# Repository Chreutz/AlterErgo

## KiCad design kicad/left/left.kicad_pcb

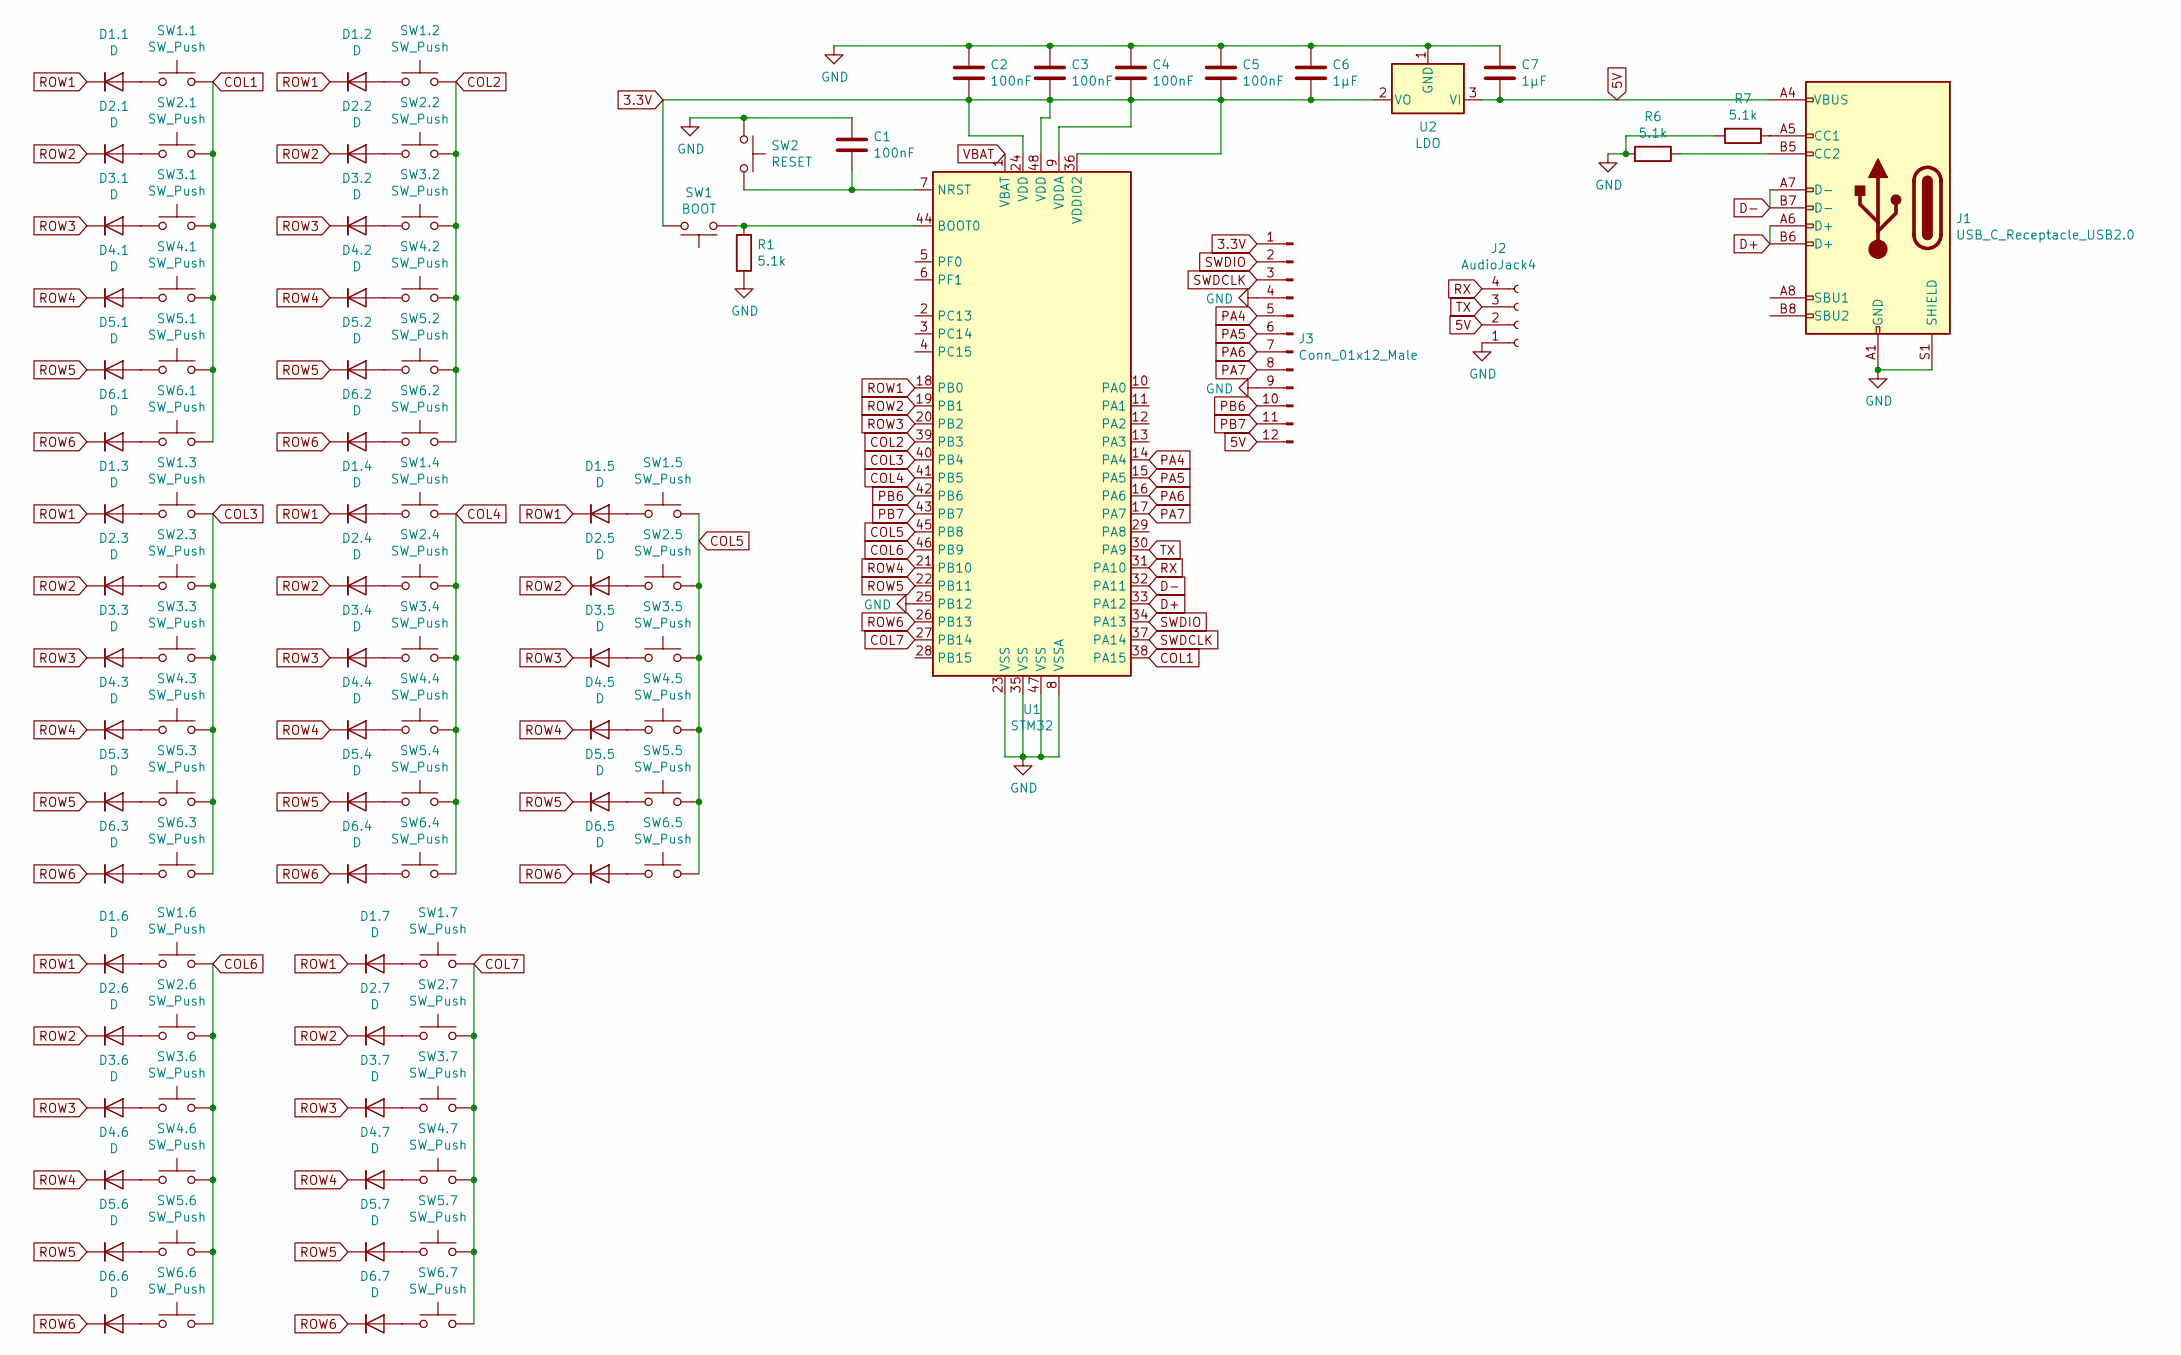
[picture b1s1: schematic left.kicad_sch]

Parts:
C1, C2, C3, C4, C5: 100nF; C_0805_2012Metric_Pad1.18x1.45mm_HandSolder
C6, C7: 1µF; C_0805_2012Metric_Pad1.18x1.45mm_HandSolder
D1.1, D1.2, D1.3, D1.4, D1.5, D1.6, D1.7, D2.1, D2.2, D2.3, D2.4, D2.5, D2.6, D2.7, D3.1, D3.2, D3.3, D3.4, D3.5, D3.6, D3.7, D4.1, D4.2, D4.3, D4.4, D4.5, D4.6, D4.7, D5.1, D5.2, D5.3, D5.4, D5.5, D5.6, D5.7, D6.1, D6.2, D6.3, D6.4, D6.5, D6.6, D6.7: D; D_SOD-323_HandSoldering
J1: USB_C_Receptacle_USB2.0; USB_C_Receptacle_HRO_TYPE-C-31-M-12
J2: AudioJack4; TRRS-PJ-320A-no-Fmask
J3: Conn_01x12_Male; Harwin_M20-89012xx_1x12_P2.54mm_Horizontal
R1, R6, R7: 5.1k; R_0805_2012Metric_Pad1.20x1.40mm_HandSolder
SW1: BOOT; SW_SPST_CK_RS282G05A3
SW1.1, SW1.2, SW1.3, SW1.4, SW1.5, SW1.6, SW1.7, SW2.1, SW2.2, SW2.3, SW2.4, SW2.5, SW2.6, SW2.7, SW3.1, SW3.2, SW3.3, SW3.4, SW3.5, SW3.6, SW3.7, SW4.1, SW4.2, SW4.3, SW4.4, SW4.5, SW4.6, SW4.7, SW5.1, SW5.2, SW5.3, SW5.4, SW5.5, SW5.6, SW5.7, SW6.1, SW6.2, SW6.3, SW6.4, SW6.5, SW6.6, SW6.7: SW_Push; CherryMX_Choc_1u
SW2: RESET; SW_SPST_CK_RS282G05A3
U1: STM32; LQFP-48_7x7mm_P0.5mm
U2: LDO; SOT-23

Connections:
3.3V: C2.2, C3.2, C4.2, C5.2, C6.2, J3.1, SW1.2, U1.9 (VDDA), U1.24 (VDD), U1.36 (VDDIO2), U1.48 (VDD), U2.2 (VO)
5V: C7.2, J1.A4 (VBUS), J1.A9 (VBUS), J1.B4 (VBUS), J1.B9 (VBUS), J2.2, J3.12, U2.3 (VI)
COL1: SW1.1.2, SW2.1.2, SW3.1.2, SW4.1.2, SW5.1.2, SW6.1.2, U1.38 (PA15)
COL2: SW1.2.2, SW2.2.2, SW3.2.2, SW4.2.2, SW5.2.2, SW6.2.2, U1.39 (PB3)
COL3: SW1.3.2, SW2.3.2, SW3.3.2, SW4.3.2, SW5.3.2, SW6.3.2, U1.40 (PB4)
COL4: SW1.4.2, SW2.4.2, SW3.4.2, SW4.4.2, SW5.4.2, SW6.4.2, U1.41 (PB5)
COL5: SW1.5.2, SW2.5.2, SW3.5.2, SW4.5.2, SW5.5.2, SW6.5.2, U1.45 (PB8)
COL6: SW1.6.2, SW2.6.2, SW3.6.2, SW4.6.2, SW5.6.2, SW6.6.2, U1.46 (PB9)
COL7: SW1.7.2, SW2.7.2, SW3.7.2, SW4.7.2, SW5.7.2, SW6.7.2, U1.27 (PB14)
D+: J1.A6 (D+), J1.B6 (D+), U1.33 (PA12)
D-: J1.A7 (D-), J1.B7 (D-), U1.32 (PA11)
GND: C1.1, C2.1, C3.1, C4.1, C5.1, C6.1, C7.1, J1.A1 (GND), J1.A12 (GND), J1.B1 (GND), J1.B12 (GND), J1.S1 (SHIELD), J2.1, J3.4, J3.9, R1.2, R6.2, R7.2, SW2.1, U1.8 (VSSA), U1.23 (VSS), U1.25 (PB12), U1.35 (VSS), U1.47 (VSS), U2.1 (GND)
unnamed: C1.2, SW2.2, U1.7 (NRST)
unnamed: D1.1.2 (A), SW1.1.1
unnamed: D1.2.2 (A), SW1.2.1
unnamed: D1.3.2 (A), SW1.3.1
unnamed: D1.4.2 (A), SW1.4.1
unnamed: D1.5.2 (A), SW1.5.1
unnamed: D1.6.2 (A), SW1.6.1
unnamed: D1.7.2 (A), SW1.7.1
unnamed: D2.1.2 (A), SW2.1.1
unnamed: D2.2.2 (A), SW2.2.1
unnamed: D2.3.2 (A), SW2.3.1
unnamed: D2.4.2 (A), SW2.4.1
unnamed: D2.5.2 (A), SW2.5.1
unnamed: D2.6.2 (A), SW2.6.1
unnamed: D2.7.2 (A), SW2.7.1
unnamed: D3.1.2 (A), SW3.1.1
unnamed: D3.2.2 (A), SW3.2.1
unnamed: D3.3.2 (A), SW3.3.1
unnamed: D3.4.2 (A), SW3.4.1
unnamed: D3.5.2 (A), SW3.5.1
unnamed: D3.6.2 (A), SW3.6.1
unnamed: D3.7.2 (A), SW3.7.1
unnamed: D4.1.2 (A), SW4.1.1
unnamed: D4.2.2 (A), SW4.2.1
unnamed: D4.3.2 (A), SW4.3.1
unnamed: D4.4.2 (A), SW4.4.1
unnamed: D4.5.2 (A), SW4.5.1
unnamed: D4.6.2 (A), SW4.6.1
unnamed: D4.7.2 (A), SW4.7.1
unnamed: D5.1.2 (A), SW5.1.1
unnamed: D5.2.2 (A), SW5.2.1
unnamed: D5.3.2 (A), SW5.3.1
unnamed: D5.4.2 (A), SW5.4.1
unnamed: D5.5.2 (A), SW5.5.1
unnamed: D5.6.2 (A), SW5.6.1
unnamed: D5.7.2 (A), SW5.7.1
unnamed: D6.1.2 (A), SW6.1.1
unnamed: D6.2.2 (A), SW6.2.1
unnamed: D6.3.2 (A), SW6.3.1
unnamed: D6.4.2 (A), SW6.4.1
unnamed: D6.5.2 (A), SW6.5.1
unnamed: D6.6.2 (A), SW6.6.1
unnamed: D6.7.2 (A), SW6.7.1
unnamed: J1.A5 (CC1), R7.1
unnamed: J1.B5 (CC2), R6.1
unnamed: R1.1, SW1.1, U1.44 (BOOT0)
PA4: J3.5, U1.14 (PA4)
PA5: J3.6, U1.15 (PA5)
PA6: J3.7, U1.16 (PA6)
PA7: J3.8, U1.17 (PA7)
PB6: J3.10, U1.42 (PB6)
PB7: J3.11, U1.43 (PB7)
ROW1: D1.1.1 (K), D1.2.1 (K), D1.3.1 (K), D1.4.1 (K), D1.5.1 (K), D1.6.1 (K), D1.7.1 (K), U1.18 (PB0)
ROW2: D2.1.1 (K), D2.2.1 (K), D2.3.1 (K), D2.4.1 (K), D2.5.1 (K), D2.6.1 (K), D2.7.1 (K), U1.19 (PB1)
ROW3: D3.1.1 (K), D3.2.1 (K), D3.3.1 (K), D3.4.1 (K), D3.5.1 (K), D3.6.1 (K), D3.7.1 (K), U1.20 (PB2)
ROW4: D4.1.1 (K), D4.2.1 (K), D4.3.1 (K), D4.4.1 (K), D4.5.1 (K), D4.6.1 (K), D4.7.1 (K), U1.21 (PB10)
ROW5: D5.1.1 (K), D5.2.1 (K), D5.3.1 (K), D5.4.1 (K), D5.5.1 (K), D5.6.1 (K), D5.7.1 (K), U1.22 (PB11)
ROW6: D6.1.1 (K), D6.2.1 (K), D6.3.1 (K), D6.4.1 (K), D6.5.1 (K), D6.6.1 (K), D6.7.1 (K), U1.26 (PB13)
RX: J2.4, U1.31 (PA10)
SWDCLK: J3.3, U1.37 (PA14)
SWDIO: J3.2, U1.34 (PA13)
TX: J2.3, U1.30 (PA9)
VBAT: U1.1 (VBAT)

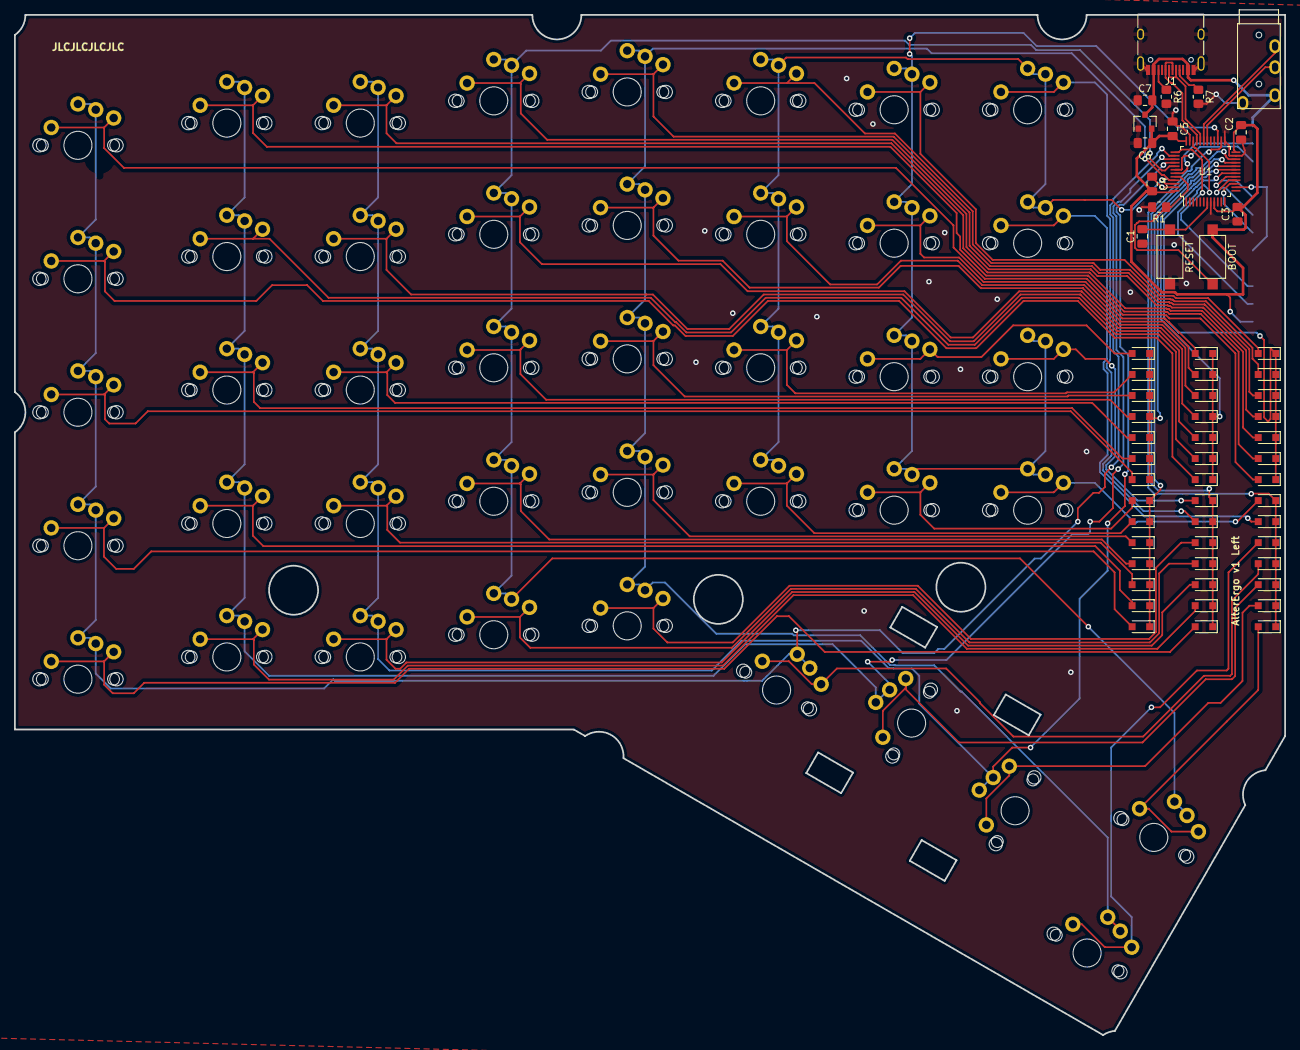
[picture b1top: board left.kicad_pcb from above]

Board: 2 copper layers, 181.3 x 145.6 mm, 101 parts (1 on the bottom side), 74 nets.

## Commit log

2023-04-27 Added kicad PCB project
